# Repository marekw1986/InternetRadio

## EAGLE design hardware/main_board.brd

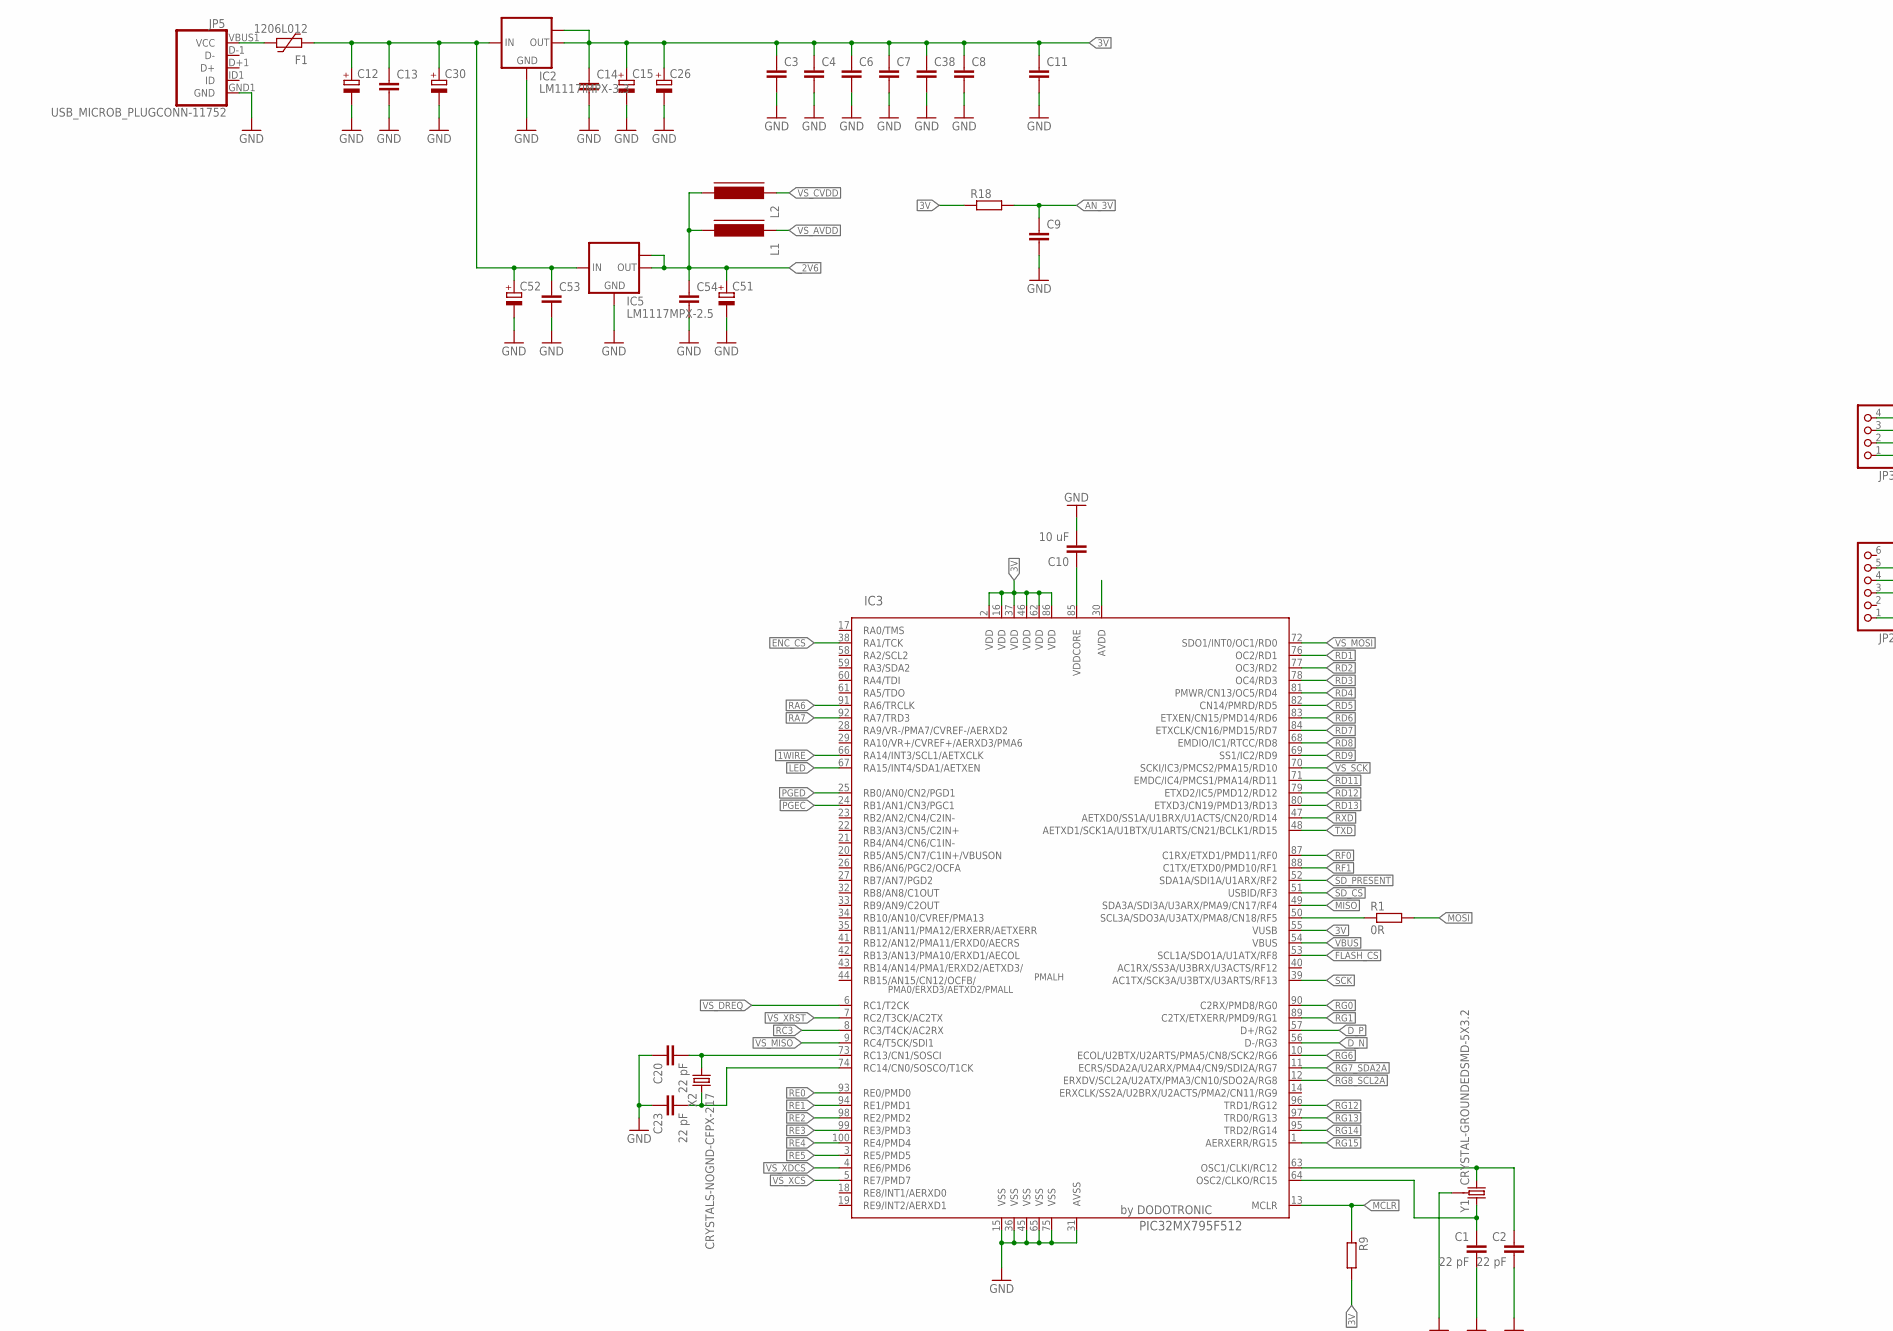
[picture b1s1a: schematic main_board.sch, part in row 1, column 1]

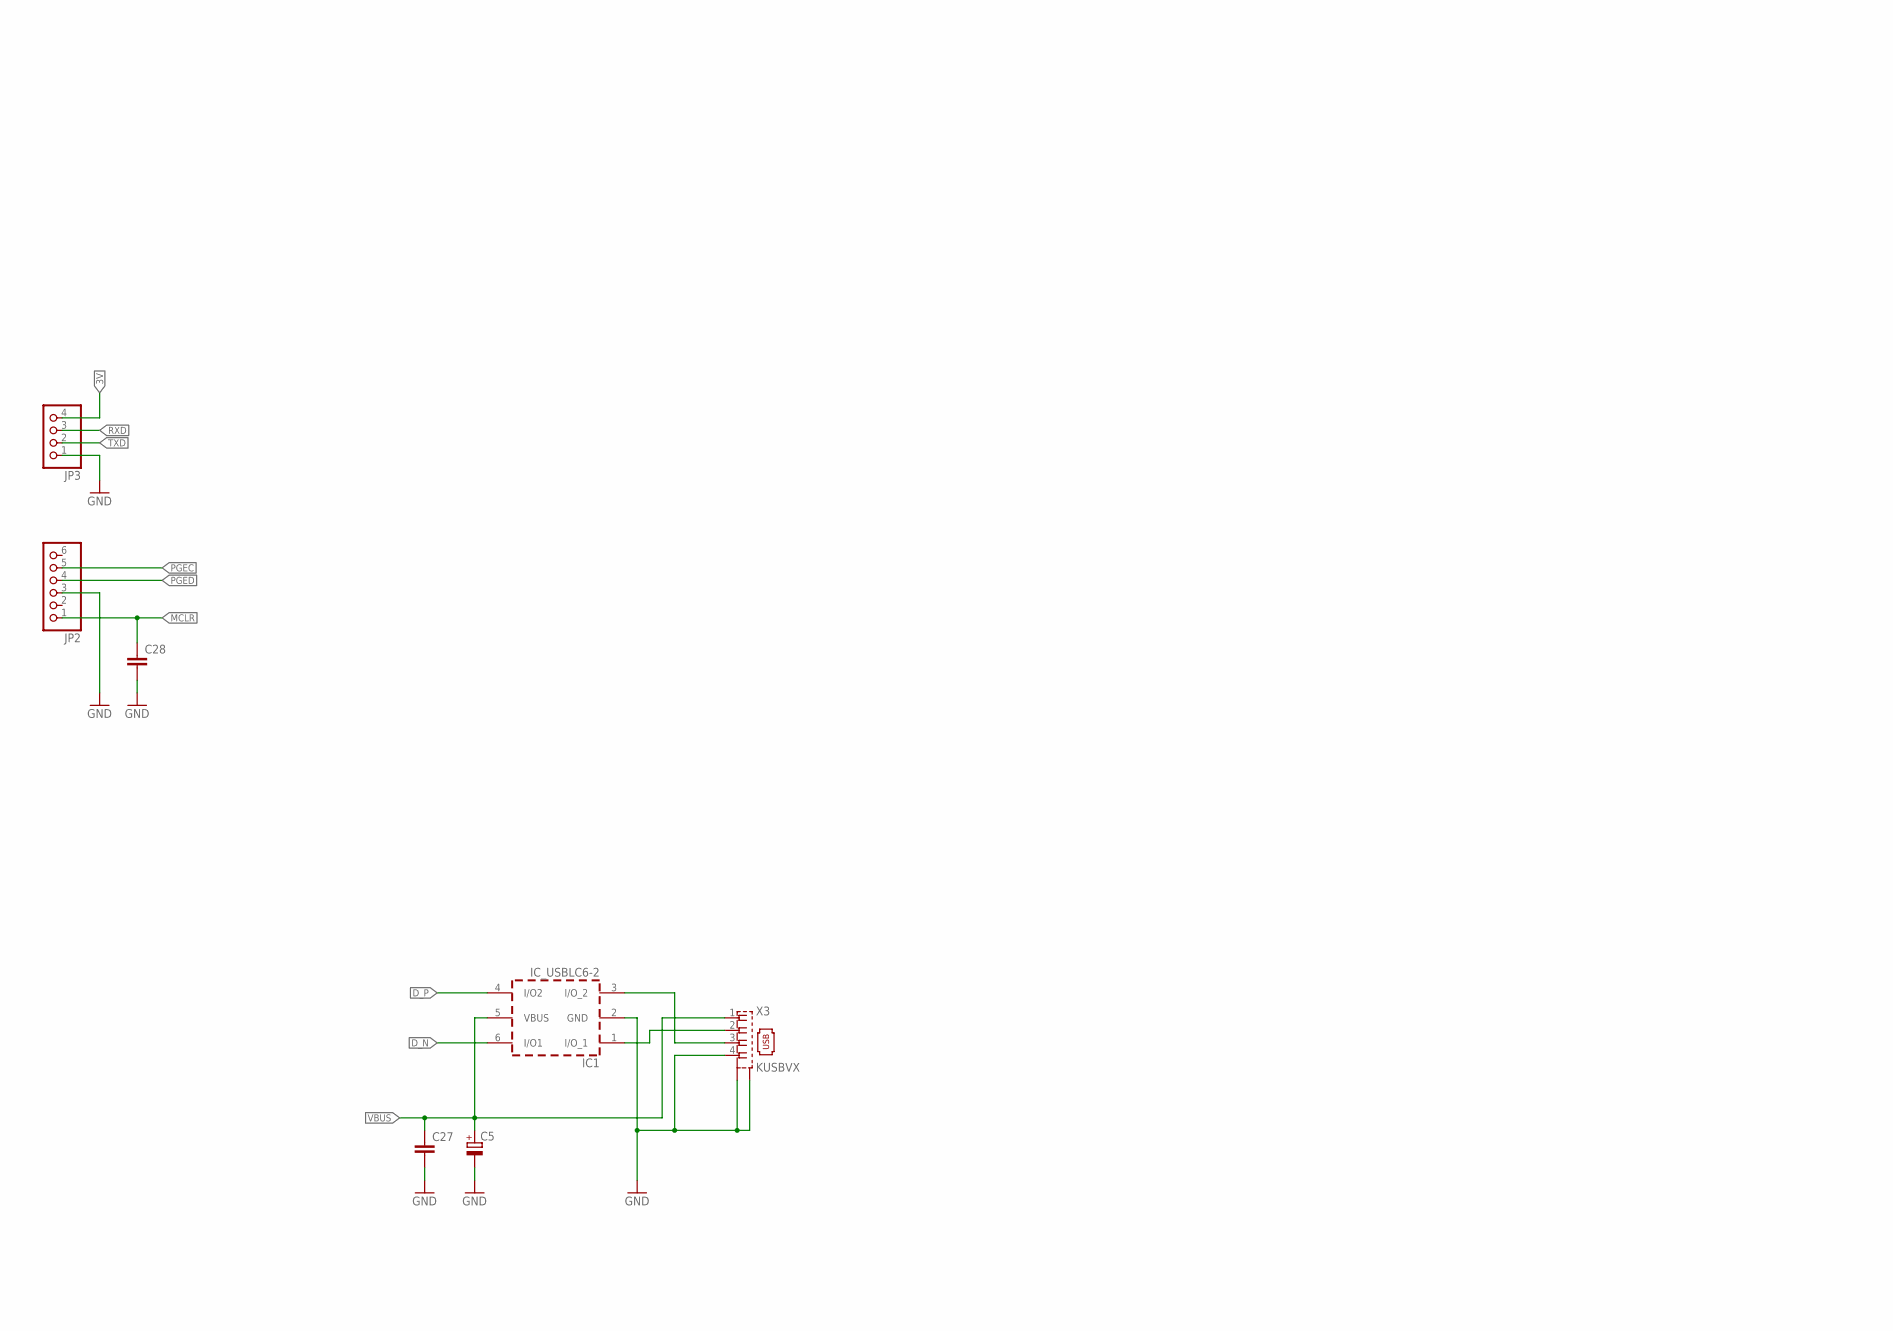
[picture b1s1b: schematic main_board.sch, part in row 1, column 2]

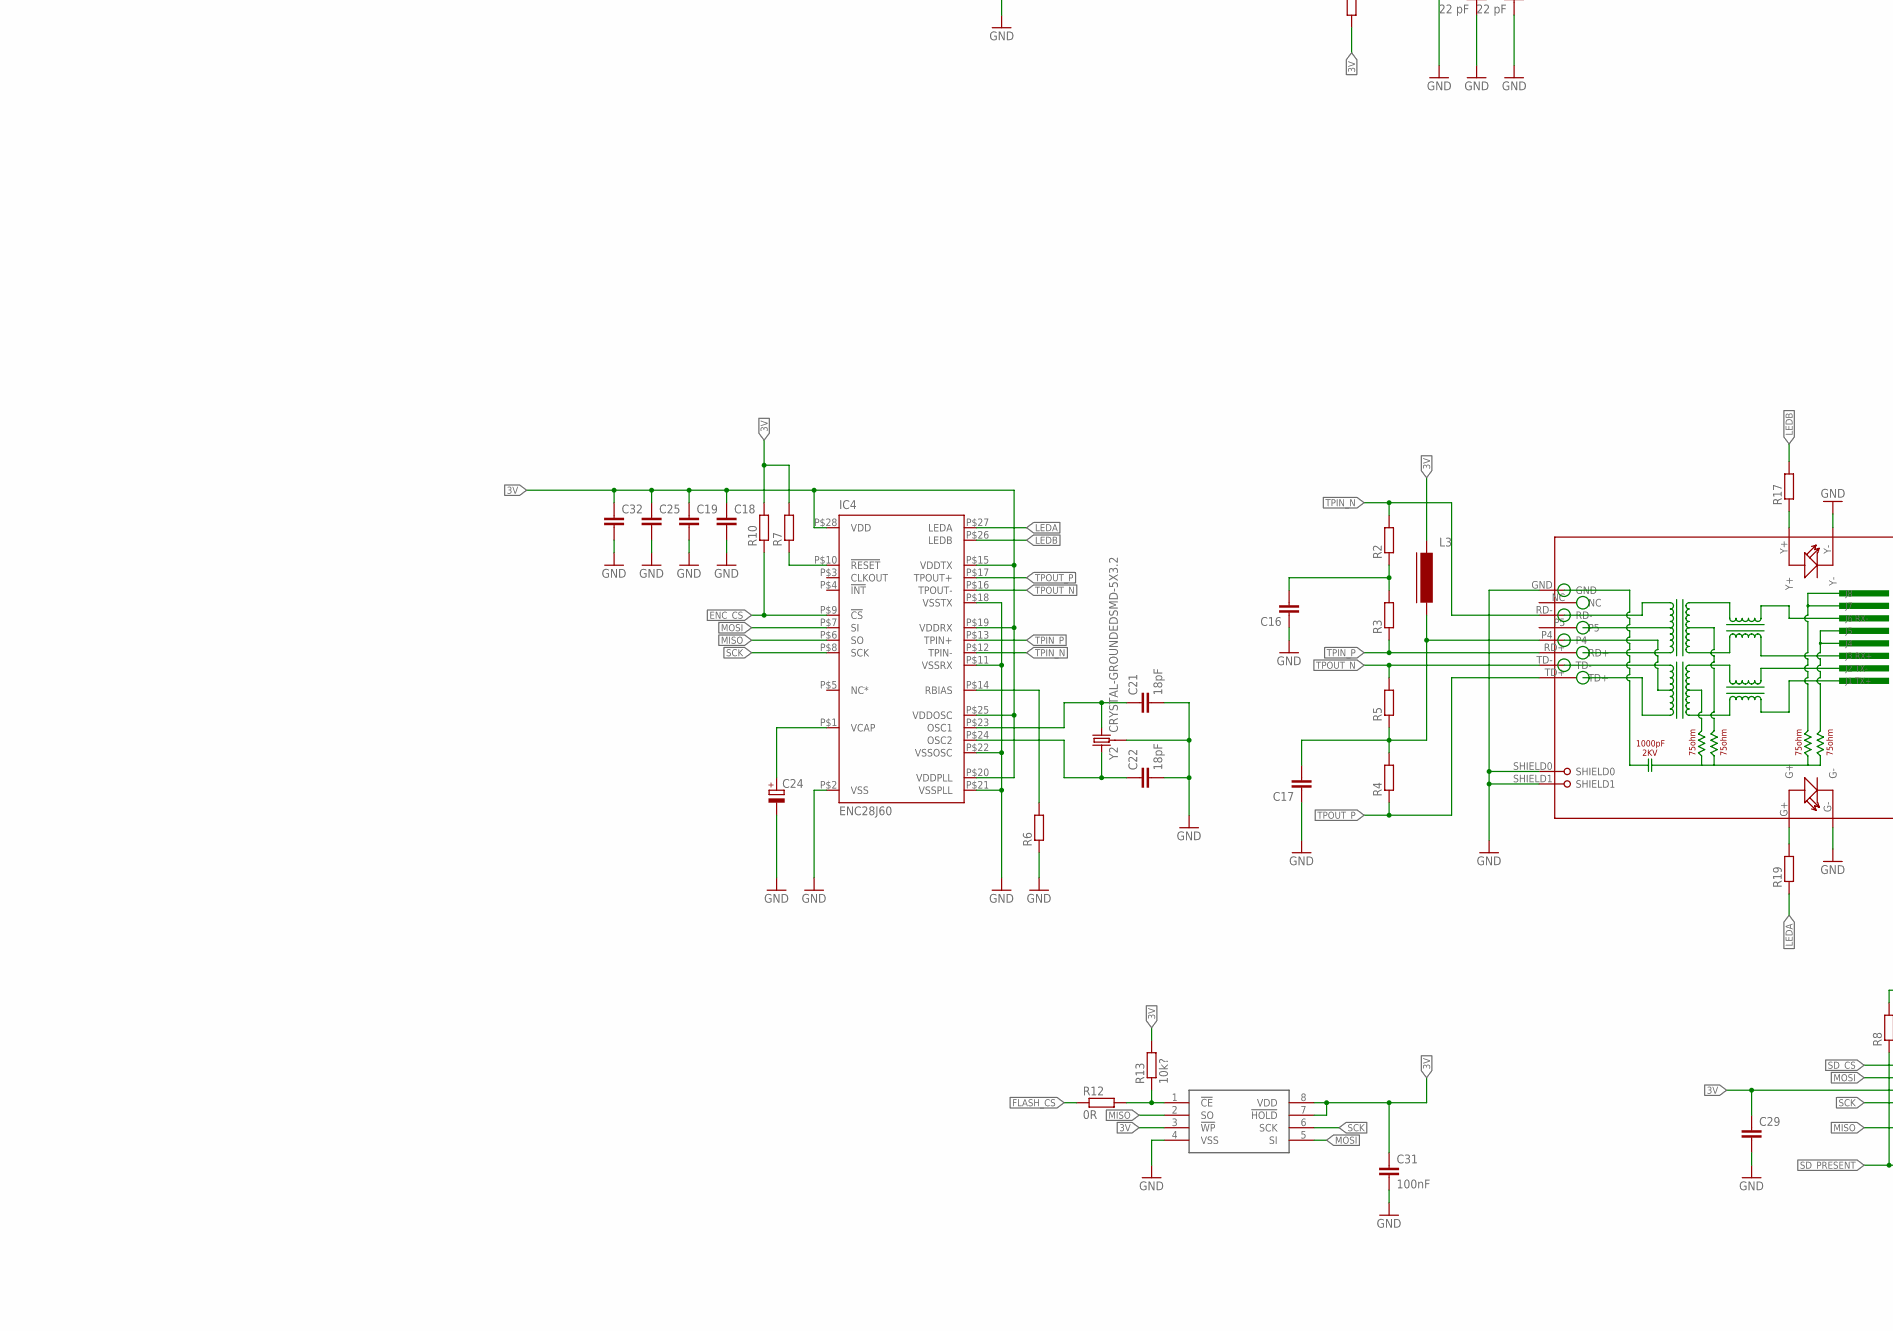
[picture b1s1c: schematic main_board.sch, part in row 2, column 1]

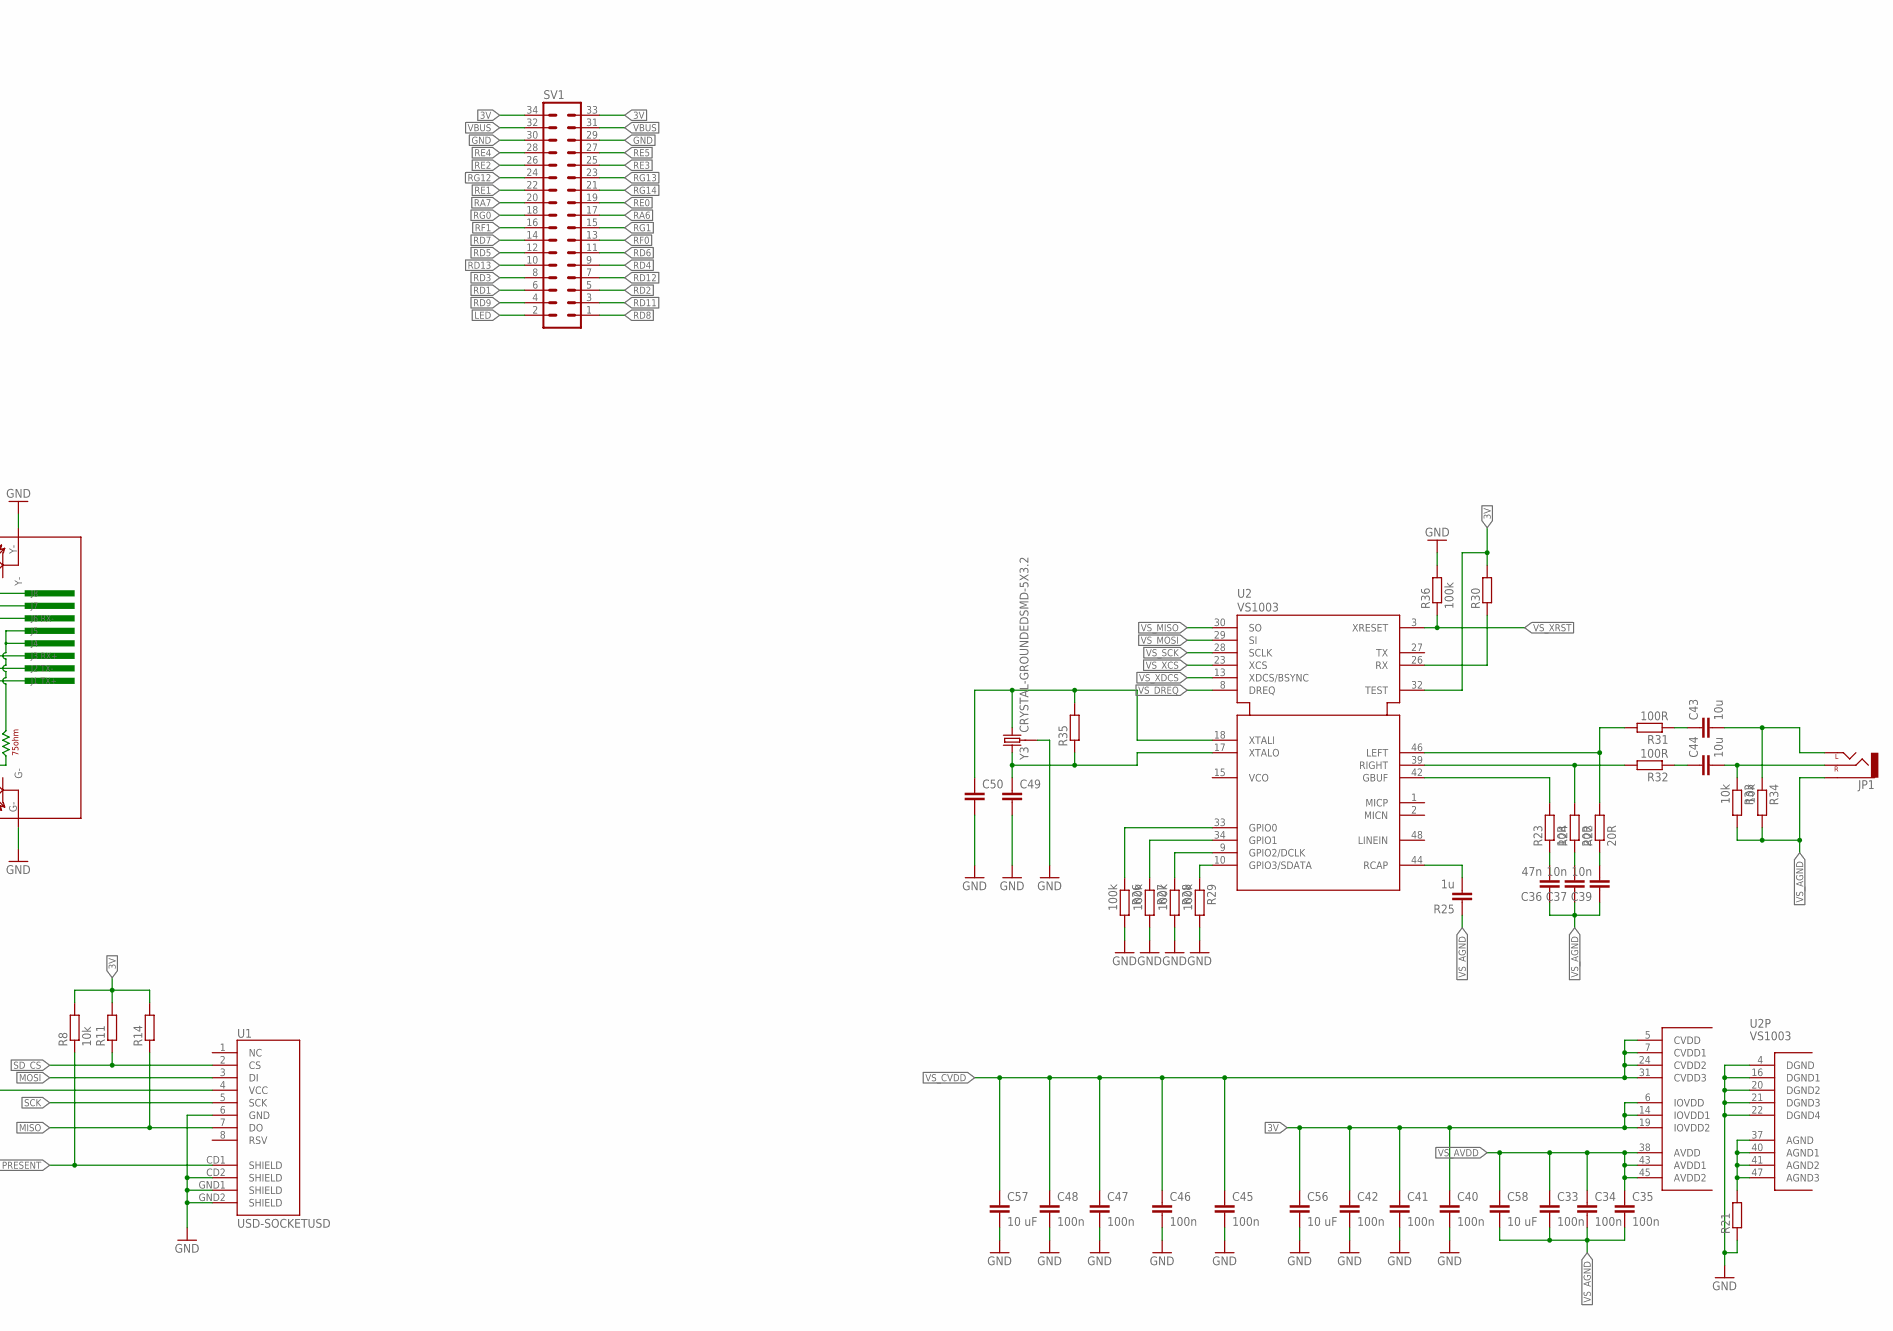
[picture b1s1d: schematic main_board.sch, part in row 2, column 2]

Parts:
C1, C2, C20, C23: 22 pF; C0603
C3, C4, C6, C7, C8, C9, C11, C18, C32, C38: C-EUC0402; C0402
C5, C24, C26, C30: CPOL-EUSMCA; SMC_A
C10, C56, C57, C58: 10 uF; C0603
C12, C15, C51, C52: CPOL-EUSMCB; SMC_B
C13, C14, C16, C17, C19, C25, C27, C28, C29, C49, C50: C-EUC0603; C0603
C21, C22: 18pF; C0603
C31: 100nF; C0603
C33, C34, C35, C46, C47, C48: 100n; C0603
C36: 47n; C0603
C37, C39: 10n; C0603
C40, C41, C42, C45: 100n; C0402
C43, C44: 10u; C0603
C53, C54: C-EUC1206; C1206
F1: 1206L012; 1206L
IC1: IC_USBLC6-2; SOT-23-6L
IC2: LM1117IMPX-3.3; SOT223
IC3: PIC32MX795F512; TQFP100_12X12
IC4: ENC28J60; TSSOP28W
IC5: LM1117MPX-2.5; SOT223
JP1: AUDIO-JACKAUDIO_JACK2; AUDIO-JACK2
JP2: PINHD-1X6; 1X06
JP3: PINHD-1X4; 1X04
JP5: USB_MICROB_PLUGCONN-11752; USB-B-MICRO-SMD_V03
L1, L2, L3: FERRITE-0805; FB805
R1, R12: 0R; R0603
R2, R3, R4, R5, R9, R10, R11, R14, R21, R35: R-EU_R0603; R0603
R6, R18: R-EU_R0805; R0805
R7: R-EU_R0402; R0402
R8, R33, R34: 10k; R0603
R13: 10k?; R0603
R17, R19: R-EU_R1206; R1206
R22, R24: 20R; R0603
R23: 10R; R0603
R25: 1u; C0603
R26, R27, R28, R29: 100k; R0402
R30: R-EU_0204/7; 0204/7
R31, R32: 100R; R0603
R36: 100k; R0603
RJ1: HR911105A
SV1: ML34L
U1: USD-SOCKETUSD; USD-SOCKET-PP
U2: VS1003; LQFP48
U$2: SST25VF016BSO8M; SO-08M
X2: CRYSTALS-NOGND-CFPX-217; 3.2X1.5-2-PAD
X3: KUSBVX
Y1, Y2, Y3: CRYSTAL-GROUNDEDSMD-5X3.2; CRYSTAL-SMD-5X3.2-4PAD

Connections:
1WIRE: IC3.66 (RA14/INT3/SCL1/AETXCLK)
3V: C3.1, C4.1, C6.1, C7.1, C8.1, C11.1, C14.1, C15.+, C18.1, C19.1, C25.1, C26.+, C29.1, C31.1, C32.1, C38.1, C40.1, C41.1, C42.1, C56.1, IC2.2 (OUT), IC2.TAB (OUT1), IC3.2 (VDD), IC3.16 (VDD), IC3.37 (VDD), IC3.46 (VDD), IC3.55 (VUSB), IC3.62 (VDD), IC3.86 (VDD), IC4.P$15 (VDDTX), IC4.P$19 (VDDRX), IC4.P$20 (VDDPLL), IC4.P$25 (VDDOSC), IC4.P$28 (VDD), JP3.4, L3.1, R7.2, R8.2, R9.2, R10.2, R11.2, R13.2, R14.2, R18.1, R30.2, SV1.33, SV1.34, U1.4 (VCC), U2.6 (IOVDD), U2.14 (IOVDD1), U2.19 (IOVDD2), U2.32 (TEST), U$2.3 (!WP), U$2.7 (!HOLD), U$2.8 (VDD)
AN_3V: C9.1, IC3.30 (AVDD), R18.2
CE1: R12.2, R13.1, U$2.1 (!CE)
D2_N: IC1.1 (I/O_1), X3.2
D2_P: IC1.3 (I/O_2), X3.3
D_N: IC1.6 (I/O1), IC3.56 (D-/RG3)
D_P: IC1.4 (I/O2), IC3.57 (D+/RG2)
ENC_CS: IC3.38 (RA1/TCK), IC4.P$9 (!CS), R10.1
ENC_RST: IC4.P$10 (!RESET), R7.1
FLASH_CS: IC3.53 (SCL1A/SDO1A/U1ATX/RF8), R12.1
GND: C1.2, C2.2, C3.2, C4.2, C5.-, C6.2, C7.2, C8.2, C9.2, C10.2, C11.2, C12.-, C13.2, C14.2, C15.-, C16.1, C17.1, C18.2, C19.2, C20.1, C21.2, C22.2, C23.1, C24.-, C25.2, C26.-, C27.2, C28.2, C29.2, C30.-, C31.2, C32.2, C38.2, C40.2, C41.2, C42.2, C45.2, C46.2, C47.2, C48.2, C49.2, C50.2, C51.-, C52.-, C53.2, C54.2, C56.2, C57.2, IC1.2 (GND), IC2.1 (GND), IC3.15 (VSS), IC3.31 (AVSS), IC3.36 (VSS), IC3.45 (VSS), IC3.65 (VSS), IC3.75 (VSS), IC4.P$2 (VSS), IC4.P$11 (VSSRX), IC4.P$18 (VSSTX), IC4.P$21 (VSSPLL), IC4.P$22 (VSSOSC), IC5.1 (GND), JP2.3, JP3.1, JP5.GND1 (GND), R6.1, R21.1, R26.2, R27.2, R28.2, R29.2, R36.2, RJ1.G-, RJ1.GND, RJ1.SHIELD0, RJ1.SHIELD1, RJ1.Y-, SV1.29, SV1.30, U1.6 (GND), U1.CD2 (SHIELD), U1.GND1 (SHIELD), U1.GND2 (SHIELD), U2.4 (DGND), U2.16 (DGND1), U2.20 (DGND2), U2.21 (DGND3), U2.22 (DGND4), U$2.4 (VSS), X3.4, X3.M1 (S1), X3.M2 (S2), Y1.2 (3), Y1.4 (3), Y2.2 (3), Y2.4 (3), Y3.2 (3), Y3.4 (3)
LED: IC3.67 (RA15/INT4/SDA1/AETXEN), SV1.2
LEDA: IC4.P$27 (LEDA), R19.1
LEDB: IC4.P$26 (LEDB), R17.2
MCLR: C28.1, IC3.13 (MCLR), JP2.1, R9.1
MISO: IC3.49 (SDA3A/SDI3A/U3ARX/PMA9/CN17/RF4), IC4.P$6 (SO), R14.1, U1.7 (DO), U$2.2 (SO)
MOSI: IC4.P$7 (SI), R1.2, U1.3 (DI), U$2.5 (SI)
unnamed: C16.2, R2.1, R3.2
unnamed: IC3.50 (SCL3A/SDO3A/U3ATX/PMA8/CN18/RF5), R1.1
unnamed: C17.2, L3.2, R4.2, R5.1, RJ1.P4
unnamed: C10.1, IC3.85 (VDDCORE)
unnamed: IC4.P$14 (RBIAS), R6.2
unnamed: F1.1, JP5.VBUS1 (VCC)
unnamed: C36.2, R23.1
unnamed: C21.1, IC4.P$23 (OSC1), Y2.1 (2)
unnamed: C22.1, IC4.P$24 (OSC2), Y2.3 (1)
unnamed: C24.+, IC4.P$1 (VCAP)
unnamed: R17.1, RJ1.Y+
unnamed: R19.2, RJ1.G+
OSC1: C2.1, IC3.63 (OSC1/CLKI/RC12), Y1.1 (2)
OSC2: C1.1, IC3.64 (OSC2/CLKO/RC15), Y1.3 (1)
PGEC: IC3.24 (RB1/AN1/CN3/PGC1), JP2.5
PGED: IC3.25 (RB0/AN0/CN2/PGD1), JP2.4
RA6: IC3.91 (RA6/TRCLK), SV1.17
RA7: IC3.92 (RA7/TRD3), SV1.20
RC3: IC3.8 (RC3/T4CK/AC2RX)
RD1: IC3.76 (OC2/RD1), SV1.6
RD2: IC3.77 (OC3/RD2), SV1.5
RD3: IC3.78 (OC4/RD3), SV1.8
RD4: IC3.81 (PMWR/CN13/OC5/RD4), SV1.9
RD5: IC3.82 (CN14/PMRD/RD5), SV1.12
RD6: IC3.83 (ETXEN/CN15/PMD14/RD6), SV1.11
RD7: IC3.84 (ETXCLK/CN16/PMD15/RD7), SV1.14
RD8: IC3.68 (EMDIO/IC1/RTCC/RD8), SV1.1
RD9: IC3.69 (SS1/IC2/RD9), SV1.4
RD11: IC3.71 (EMDC/IC4/PMCS1/PMA14/RD11), SV1.3
RD12: IC3.79 (ETXD2/IC5/PMD12/RD12), SV1.7
RD13: IC3.80 (ETXD3/CN19/PMD13/RD13), SV1.10
RE0: IC3.93 (RE0/PMD0), SV1.19
RE1: IC3.94 (RE1/PMD1), SV1.22
RE2: IC3.98 (RE2/PMD2), SV1.26
RE3: IC3.99 (RE3/PMD3), SV1.25
RE4: IC3.100 (RE4/PMD4), SV1.28
RE5: IC3.3 (RE5/PMD5), SV1.27
RF0: IC3.87 (C1RX/ETXD1/PMD11/RF0), SV1.13
RF1: IC3.88 (C1TX/ETXD0/PMD10/RF1), SV1.16
RG0: IC3.90 (C2RX/PMD8/RG0), SV1.18
RG1: IC3.89 (C2TX/ETXERR/PMD9/RG1), SV1.15
RG6: IC3.10 (ECOL/U2BTX/U2ARTS/PMA5/CN8/SCK2/RG6)
RG7_SDA2A: IC3.11 (ECRS/SDA2A/U2ARX/PMA4/CN9/SDI2A/RG7)
RG8_SCL2A: IC3.12 (ERXDV/SCL2A/U2ATX/PMA3/CN10/SDO2A/RG8)
RG12: IC3.96 (TRD1/RG12), SV1.24
RG13: IC3.97 (TRD0/RG13), SV1.23
RG14: IC3.95 (TRD2/RG14), SV1.21
RG15: IC3.1 (AERXERR/RG15)
RXD: IC3.47 (AETXD0/SS1A/U1BRX/U1ACTS/CN20/RD14), JP3.3
SCK: IC3.39 (AC1TX/SCK3A/U3BTX/U3ARTS/RF13), IC4.P$8 (SCK), U1.5 (SCK), U$2.6 (SCK)
SD_CS: IC3.51 (USBID/RF3), R11.1, U1.2 (CS)
SD_PRESENT: IC3.52 (SDA1A/SDI1A/U1ARX/RF2), R8.1, U1.CD1 (SHIELD)
SOSCI: C20.2, IC3.73 (RC13/CN1/SOSCI), X2.1
SOSCO: C23.2, IC3.74 (RC14/CN0/SOSCO/T1CK), X2.2
TPIN_N: IC4.P$12 (TPIN-), R2.2, RJ1.RD-
TPIN_P: IC4.P$13 (TPIN+), R3.1, RJ1.RD+
TPOUT_N: IC4.P$16 (TPOUT-), R5.2, RJ1.TD-
TPOUT_P: IC4.P$17 (TPOUT+), R4.1, RJ1.TD+
TXD: IC3.48 (AETXD1/SCK1A/U1BTX/U1ARTS/CN21/BCLK1/RD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), JP3.2
VBUS: C5.+, C12.+, C13.1, C27.1, C30.+, C52.+, C53.1, F1.2, IC1.5 (VBUS), IC2.3 (IN), IC3.54 (VBUS), IC5.3 (IN), SV1.31, SV1.32, X3.1
VS_AGND: C33.2, C34.2, C35.2, C36.1, C37.1, C39.1, C58.2, JP1.SLEEVE, R21.2, R25.1, R33.2, R34.2, U2.37 (AGND), U2.40 (AGND1), U2.41 (AGND2), U2.47 (AGND3)
VS_AVDD: C33.1, C34.1, C35.1, C58.1, L1.1, U2.38 (AVDD), U2.43 (AVDD1), U2.45 (AVDD2)
VS_CVDD: C45.1, C46.1, C47.1, C48.1, C57.1, L2.1, U2.5 (CVDD), U2.7 (CVDD1), U2.24 (CVDD2), U2.31 (CVDD3)
VS_DREQ: IC3.6 (RC1/T2CK), U2.8 (DREQ)
VS_MISO: IC3.9 (RC4/T5CK/SDI1), U2.30 (SO)
VS_MOSI: IC3.72 (SDO1/INT0/OC1/RD0), U2.29 (SI)
VS_N$9: C50.1, R35.2, U2.18 (XTALI), Y3.1 (2)
VS_N$13: C49.1, R35.1, U2.17 (XTALO), Y3.3 (1)
VS_N$14: R22.2, R31.2, U2.46 (LEFT)
VS_N$15: R23.2, U2.42 (GBUF)
VS_N$16: R24.2, R32.2, U2.39 (RIGHT)
VS_N$17: R25.2, U2.44 (RCAP)
VS_N$24: C37.2, R24.1
VS_N$25: C39.2, R22.1
VS_N$26: R29.1, U2.10 (GPIO3/SDATA)
VS_N$27: R28.1, U2.9 (GPIO2/DCLK)
VS_N$28: R27.1, U2.34 (GPIO1)
VS_N$30: R26.1, U2.33 (GPIO0)
VS_N$34: R30.1, U2.26 (RX)
VS_N$35: C43.1, R31.1
VS_N$36: C44.1, R32.1
VS_N$37: C44.2, JP1.RING (RIGHT), R33.1
VS_N$38: C43.2, JP1.TIP (LEFT), R34.1
VS_SCK: IC3.70 (SCKI/IC3/PMCS2/PMA15/RD10), U2.28 (SCLK)
VS_XCS: IC3.5 (RE7/PMD7), U2.23 (XCS)
VS_XDCS: IC3.4 (RE6/PMD6), U2.13 (XDCS/BSYNC)
VS_XRST: IC3.7 (RC2/T3CK/AC2TX), R36.1, U2.3 (XRESET)
_2V6: C51.+, C54.1, IC5.2 (OUT), IC5.TAB (OUT1), L1.2, L2.2

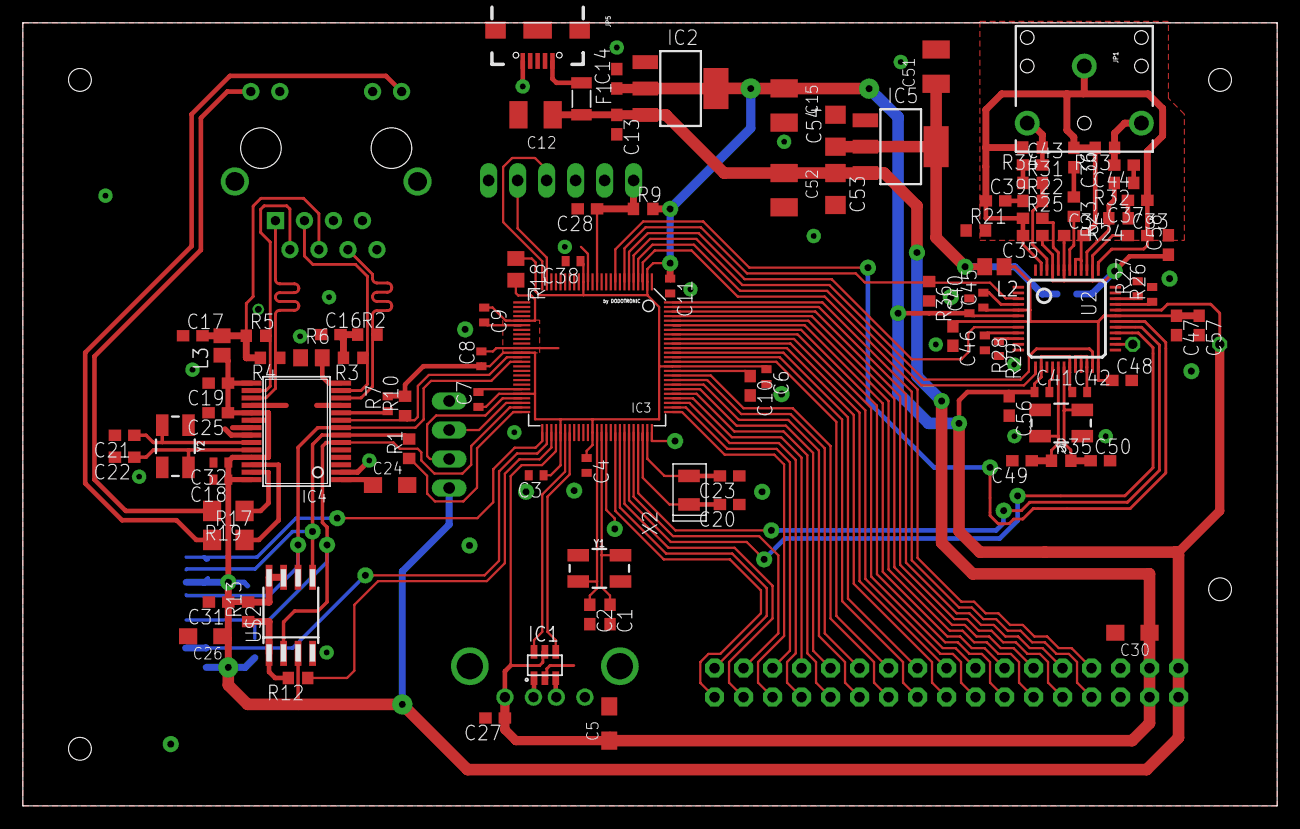
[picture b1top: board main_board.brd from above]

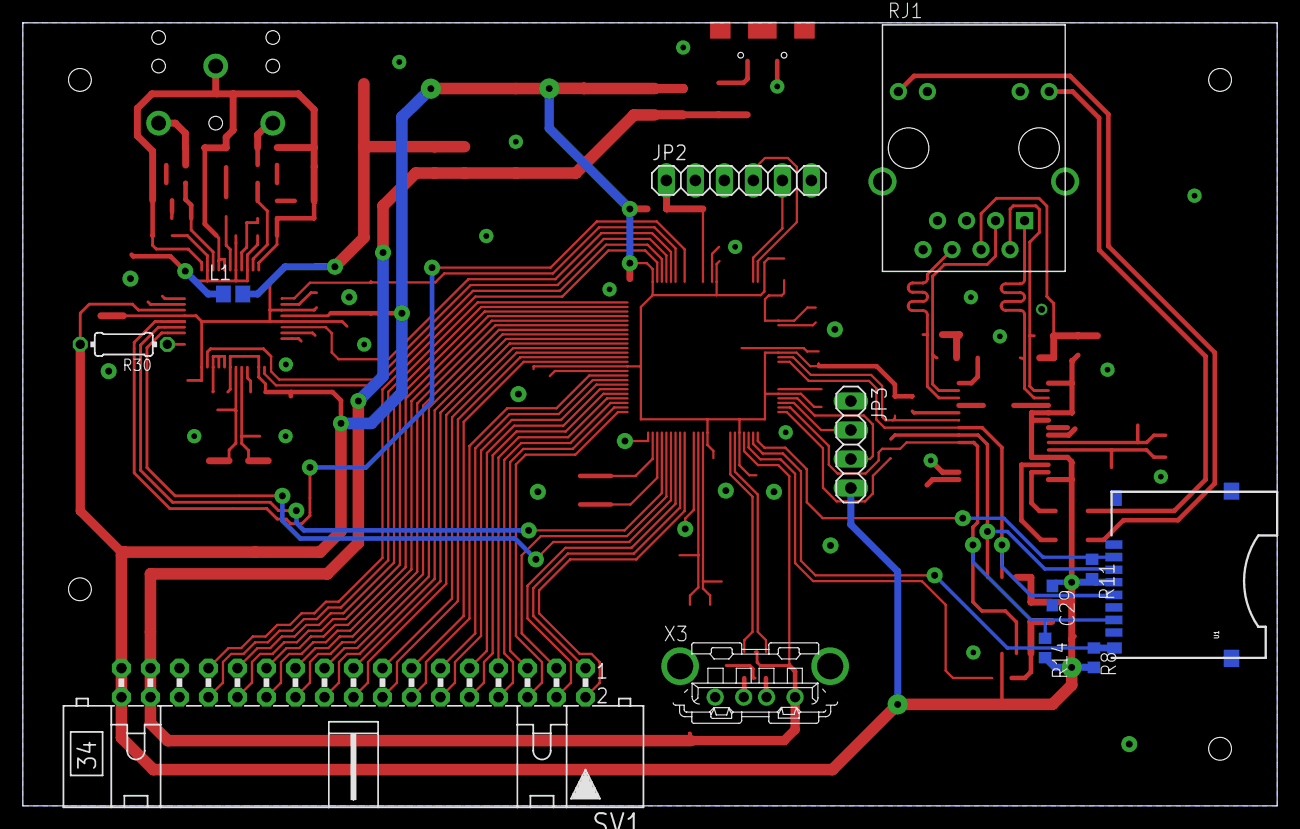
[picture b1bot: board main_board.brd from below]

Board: 2 copper layers, 109.9 x 68.6 mm, 113 parts (12 on the bottom side), 100 nets.

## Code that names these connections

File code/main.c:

/* 
 * File:   main.c
 * Author: Marek
 *
 * Created on 7 stycznia 2016, 12:22
 */

#include <xc.h>
#include <stdio.h>
#include <stdlib.h>
#include <stdint.h>
#include <p32xxxx.h>
#include <plib.h>
#include <time.h>
#include <string.h>

#include "usb/usb.h"
#include "usb/usb_host_msd.h"
#include "usb/usb_host_msd_scsi.h"
#include "fatfs/ff.h"
#include "fatfs/diskio.h"
#include "delay/delay.h"
#include "time/time.h"
#include "uart/uart.h"
#include "common.h"
#include "net/TCPIP.h"
#include "vs1003/vs1003.h"
#include "nvram/nvram.h"
#include "HardwareProfile.h"
#include "fatfs/sd.h"


#pragma config FSOSCEN = ON        // ENABLE secondary oscillator

#pragma config POSCMOD=HS          // High speed crystal mode
#pragma config FNOSC=PRIPLL        // Use Primary Oscillator with PLL (XT, HS, or EC) 
#pragma config FPLLIDIV=DIV_2      // Divide 8MHz to between 4-5MHz before PLL (now 4MHz)
#pragma config FPLLMUL=MUL_20      // Multiply with PLL (now 80MHz)
#pragma config FPLLODIV=DIV_1      // Divide After PLL (now 80 MHz)

#pragma config FWDTEN = ON         // ENABLE watchdog timer
#pragma config WDTPS = PS4096
#pragma config ICESEL = ICS_PGx1   // select pins to transfer program data on (ICSP pins)

#pragma config FVBUSONIO = OFF
#pragma config FUSBIDIO = OFF
#pragma config UPLLEN   = ON
#pragma config UPLLIDIV = DIV_2

uint8_t buffer[512];
static FATFS SpiFS;
static FATFS UsbFS;
static FATFS FatFS;
FRESULT res;
FIL fsrc;               // file objects
UINT br;         		// File R/W count


extern void GenericTCPServer(void);
static inline void init_periph (void);
void usb_write (void);

void Next_Track(FIL* File, DIR* Directory, FILINFO* File_Info);
void Send_Playback_Time();
void Send_Bitrate();
void Send_Samplerate();
void Send_Volume();
uint8_t IsPlayable(char* File_Name);

int main(int argc, char** argv) {
    
    int i;
    
    uint32_t usb_timer;
    
    DisableWDT();
    SYSTEMConfigPerformance(SYSCLK);
    init_periph();
    
    memset(buffer, 0x00, sizeof(buffer));
 
    time_init();
    MPFSInit();
    TickInit();
    uart_init();
    INTEnableSystemMultiVectoredInt();
    
    USBInitialize(0);
//    while(!USBHostMSDSCSIMediaDetect()) {
//        USBTasks(); //wait   for usb attach
//        //tutuaj trzeba zaimplentowac timout oczekiwania na mediadetect()
//    }
    
    //FormatSpiFlashDisk(); 
    
    CheckAndLoadDefaults();
    
    delay_ms(500);  //TEST
    
    res = f_mount(&SpiFS, "0:", 1);
    if (res != FR_OK) {printf("SPI Flash f_mount error code: %i\r\n", res);}
    else {printf("SPI Flash f_mount OK\r\n");}    
    
    res = f_mount(&UsbFS, "1:", 0);
    if (res != FR_OK) {printf("USB f_mount error code: %i\r\n", res);}
    else {printf("USB f_mount OK\r\n");}    
    
    res = f_mount(&FatFS, "2:", 1);
    if (res != FR_OK) {printf("f_mount error code: %i\r\n", res);}
    else {printf("f_mount OK\r\n");}
    
    StackInit();
    VS1003_begin();
    VS1003_setVolume(0x00);
    //VS1003_play_dir("2:/");
    //VS1003_play_next_http_stream_from_list();
    
//    i = sd_init();
//    printf("Result of sd_init(): %d\r\n", i);
    
    ClearWDT();
    EnableWDT();
    
    while (1) {
        
        StackTask();
        StackApplications();
        UART_RX_STR_EVENT(buffer);
        
        USBTasks();
        disk_timerproc();
        
        ClearWDT();
        
        if ((uint32_t)(millis()-usb_timer) >= 5000) {
            usb_timer = millis();
            //printf("Test, should be every 5s\r\n");
            //usb_write();
        }
        
        VS1003_handle();
    }

    return (EXIT_SUCCESS);
}


static inline void init_periph (void) {
    DDPCON = DDPCON & 0xFFFFFFF7;   // Disable JTAG
    AD1PCFG = 0xFFFF;               //All ANx inputs disabled, digitl mode only
    TRISAbits.TRISA1 = 0;           //ENC_CS is output
    LATAbits.LATA1 = 1;             //ENC_CS is high
    TRISCbits.TRISC1 = 1;           //VS_DREQ is input
    TRISCbits.TRISC2 = 0;           //VS_XRST is output
    LATCbits.LATC2 = 1;             //VS_XRST is high (it is active high)
    TRISCbits.TRISC4 = 1;           //VS_MISO is input
    TRISEbits.TRISE6 = 0;           //VS_XDCS is output
    LATEbits.LATE6 = 1;             //VS_XDCS is high
    TRISEbits.TRISE7 = 0;           //VS_XCS is output
    LATEbits.LATE7 = 1;             //VS_XCS is high
    TRISDbits.TRISD0 = 0;           //VS_MOSI is output
    TRISDbits.TRISD10 = 0;          //VS_SCK is output
    TRISDbits.TRISD14 = 1;          //RXD is input
    TRISDbits.TRISD15 = 0;          //TXD is output
    TRISFbits.TRISF2 = 1;           //SD_PRESENT is input
    TRISFbits.TRISF3 = 0;           //SD_CS is output
    LATFbits.LATF3 = 1;             //SD_CS is high
    TRISFbits.TRISF4 = 1;           //MISO is input
    TRISFbits.TRISF5 = 0;           //MOSI is output
    TRISFbits.TRISF8 = 0;           //FLASH_CS is output
    LATFbits.LATF8 = 1;             //FLASH_CS is high
    TRISFbits.TRISF13 = 0;          //SCK is output
}


void usb_write (void) { 
    FRESULT res;
    FIL file;

    res = f_open(&file, "0:/test.txt", (FA_OPEN_ALWAYS | FA_WRITE));
    if (res != FR_OK) {
        printf("f_open error code: %i\r\n", res);
        return;
    }
    if (f_size(&file) == 0) {
        f_puts("To jest pierwsza linia\r\n", &file);
    }
    else {
        res = f_lseek(&file, f_size(&file));
        if (res != FR_OK) {
            printf("f_lseek error code: %i\r\n", res); 
            f_close(&file);
            return;
        }
    }
    f_puts("test\r\n", &file);
    f_close(&file); 
}


static enum {
      EXCEP_IRQ = 0,            // interrupt
      EXCEP_AdEL = 4,            // address error exception (load or ifetch)
      EXCEP_AdES,                // address error exception (store)
      EXCEP_IBE,                // bus error (ifetch)
      EXCEP_DBE,                // bus error (load/store)
      EXCEP_Sys,                // syscall
      EXCEP_Bp,                // breakpoint
      EXCEP_RI,                // reserved instruction
      EXCEP_CpU,                // coprocessor unusable
      EXCEP_Overflow,            // arithmetic overflow
      EXCEP_Trap,                // trap (possible divide by zero)
      EXCEP_IS1 = 16,            // implementation specfic 1
      EXCEP_CEU,                // CorExtend Unuseable
      EXCEP_C2E                // coprocessor 2
  } _excep_code;


static unsigned int _epc_code;
static unsigned int _excep_addr;



void _general_exception_handler(void) {
    int i=0;
    asm volatile("mfc0 %0,$13" : "=r" (_excep_code));
    asm volatile("mfc0 %0,$14" : "=r" (_excep_addr));
  
    _excep_code = (_excep_code & 0x0000007C) >> 2;
 

	 printf("\r\n\r\n GE at %x ",_excep_addr);
	 switch(_excep_code){
        case EXCEP_IRQ: printf("interrupt");break;
        case EXCEP_AdEL: printf("address error exception (load or ifetch)");break;
        case EXCEP_AdES: printf("address error exception (store)");break;
        case EXCEP_IBE: printf("(ifetch)");break; //bus error
        case EXCEP_DBE: printf("(load/store)");break; //bus error
        case EXCEP_Sys: printf("syscall");break;
        case EXCEP_Bp: printf("breakpoint");break;
        case EXCEP_RI: printf("reserved instruction");break;
        case EXCEP_CpU: printf("coprocessor unusable");break;
        case EXCEP_Overflow: printf("arithmetic overflow");break;
        case EXCEP_Trap: printf("trap (possible divide by zero)");break;
        case EXCEP_IS1: printf("implementation specfic 1");break;
        case EXCEP_CEU: printf("CorExtend Unuseable");break;
        case EXCEP_C2E: printf("coprocessor 2");break;
      }
	  printf("\r\nExecution halted.\r\n");
      while (1) {
		printf("Waiting for WTD reset %lu\r\n",i++);
		delay_ms(1000);
      }
}

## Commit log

2020-08-25 ignored directories
2020-08-25 ignore directories
2020-08-25 cleaned
2020-09-18 PCB added
2020-12-14 PCB updated
2021-03-11 Some changes
2022-09-18 fix after IDE update
2022-09-18 updated from main project code
2022-09-18 small fix
2022-09-19 New version of VS1003 library integrated
2022-09-19 uart temp fix
2022-09-20 dir playing fix
2022-10-04 Controlling playback with HTTP POST request
2022-10-04 play.cgi added
2022-10-04 Controlling playback with webui
2022-10-06 Attempt to fix an issie with simultaneous operation of ENC and SD card
2022-10-06 SPI Flash
2022-10-08 small changes
2022-10-08 TODO.md updated
2022-10-11 MISO pull-up added
2022-10-13 Memory friendly HTTP header parser and circular buffer implemented
2022-10-13 USB playback fix
2022-10-13 USB fix
2022-10-16 memory friendly SPi Flash IO implemented and HTTP Auth reenabled
2022-10-16 FatFS updated to R0.14b
2022-10-17 SPI Flash IO bug fixed
2022-10-19 Problem with choppy playback fixed
2022-10-19 dir.json
2022-10-19 html/ui/dir.json added
2022-10-19 HTML updated
2022-10-22 USB cache reenabled to improve playback
2022-10-30 WebUI updates
2022-10-31 WebUI updated
2022-11-01 WebUI and TODO.md updated
2022-11-04 Moving stream list to file (in progress)
2022-11-04 optimization
2022-11-08 Unicode

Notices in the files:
parts and their libraries:
SparkFun-Clocks: Licensing: Creative Commons ShareAlike 4.0 International - https://creativecommons.org/licenses/by-sa/4.0
